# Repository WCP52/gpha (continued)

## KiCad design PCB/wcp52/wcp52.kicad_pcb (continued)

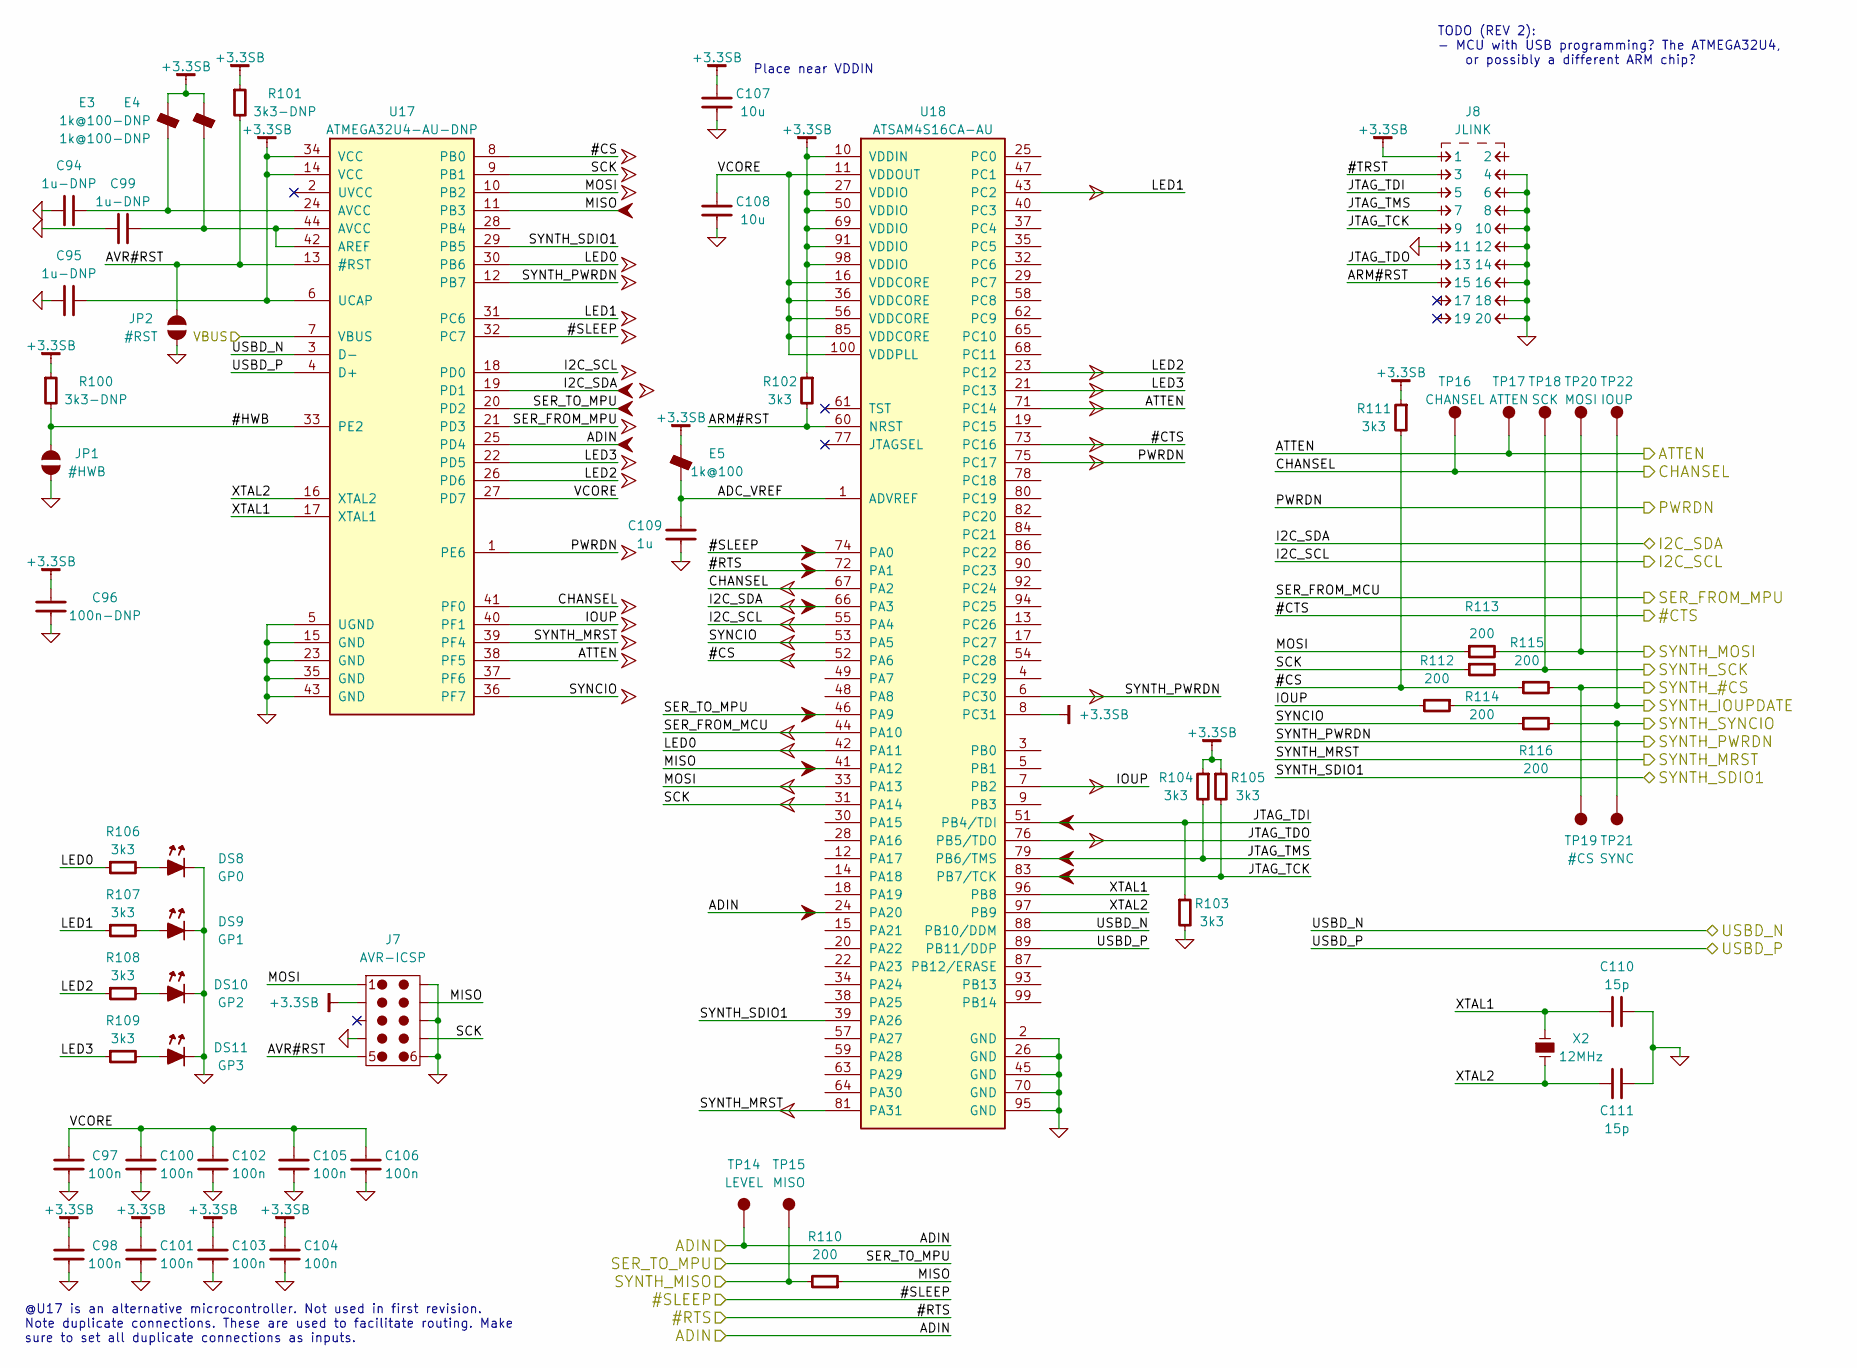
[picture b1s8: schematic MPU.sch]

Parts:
C94, C95, C99: 1u-DNP; CAPC2012X70
C96: 100n-DNP; CAPC1608X55
C97, C98, C100, C101, C102, C103, C104, C105, C106: 100n; CAPC1608X55
C107, C108: 10u; CAPC2012X70
C109: 1u; CAPC2012X70
C110, C111: 15p; CAPC1608X55
DS8: GP0; LED-0603
DS9: GP1; LED-0603
DS10: GP2; LED-0603
DS11: GP3; LED-0603
E3, E4: 1k@100-DNP; INDC1608X95
E5: 1k@100; INDC1608X95
J7: AVR-ICSP; TAGCONNECT-TC2050
J8: JLINK; CONN-100MIL-M-2x10-SHROUD
JP1: #HWB
JP2: #RST
R100, R101: 3k3-DNP; RESC1608X50
R102, R103, R104, R105, R106, R107, R108, R109, R111: 3k3; RESC1608X50
R110, R112, R113, R114, R115, R116: 200; RESC1608X50
TP14: LEVEL; TEST-SMD-SMALL
TP15: MISO; TEST-SMD-SMALL
TP16: CHANSEL; TEST-SMD-SMALL
TP17: ATTEN; TEST-SMD-SMALL
TP18: SCK; TEST-SMD-SMALL
TP19: #CS; TEST-SMD-SMALL
TP20: MOSI; TEST-SMD-SMALL
TP21: SYNC; TEST-SMD-SMALL
TP22: IOUP; TEST-SMD-SMALL
U17: ATMEGA32U4-AU-DNP; QFP80P1200X1200X120-44
U18: ATSAM4S16CA-AU; QFP50P1600X1600X160-100
X2: 12MHz; XTAL1200X480X460

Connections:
+3.3SB: C95.1, C96.1, C98.1, C101.1, C103.1, C104.1, C107.1, E3.1, E4.1, E5.1, J7.2, J8.1, R100.1, R101.1, R102.1, R104.1, R105.1, R111.1, U17.6 (UCAP), U17.14 (VCC), U17.34 (VCC), U18.8 (PC31), U18.10 (VDDIN), U18.27 (VDDIO), U18.50 (VDDIO), U18.69 (VDDIO), U18.91 (VDDIO), U18.98 (VDDIO); also elsewhere on the board
/Comm/#CTS: U18.73 (PC16); also elsewhere on the board
/Comm/#RTS: U18.72 (PA1); also elsewhere on the board
/Comm/#SLEEP: U17.32 (PC7), U18.74 (PA0); also elsewhere on the board
/Comm/IN_USBD_N: U17.3 (D-), U18.88 (PB10/DDM); also elsewhere on the board
/Comm/IN_USBD_P: U17.4 (D+), U18.89 (PB11/DDP); also elsewhere on the board
/Comm/SER_FROMUSB: U17.20 (PD2), U18.46 (PA9); also elsewhere on the board
/Comm/VBUS: U17.7 (VBUS); also elsewhere on the board
/MPU/#CS: R111.2, R115.1, U17.8 (PB0), U18.52 (PA6)
/MPU/#HWB: JP1.1, R100.2, U17.33 (PE2)
/MPU/#TRST: J8.3
/MPU/ADC_VREF: C109.1, E5.2, U18.1 (ADVREF)
/MPU/ADIN: TP14.1, U17.25 (PD4), U18.24 (PA20); also elsewhere on the board
/MPU/ARM#RST: J8.15, R102.2, U18.60 (NRST)
/MPU/ATTEN: TP17.1, U17.38 (PF5), U18.71 (PC14); also elsewhere on the board
/MPU/AVR#RST: J7.5, JP2.1, R101.2, U17.13 (#RST)
/MPU/CHANSEL: TP16.1, U17.41 (PF0), U18.67 (PA2); also elsewhere on the board
/MPU/I2C_SCL: U17.18 (PD0), U18.55 (PA4); also elsewhere on the board
/MPU/I2C_SDA: U17.19 (PD1), U18.66 (PA3); also elsewhere on the board
/MPU/IOUP: R112.2, U17.40 (PF1), U18.7 (PB2)
/MPU/JTAG_TCK: J8.9, R105.2, U18.83 (PB7/TCK)
/MPU/JTAG_TDI: J8.5, R103.1, U18.51 (PB4/TDI)
/MPU/JTAG_TDO: J8.13, U18.76 (PB5/TDO)
/MPU/JTAG_TMS: J8.7, R104.2, U18.79 (PB6/TMS)
/MPU/LED0: R106.1, U17.30 (PB6), U18.42 (PA11)
/MPU/LED1: R107.1, U17.31 (PC6), U18.43 (PC2)
/MPU/LED2: R108.1, U17.26 (PD6), U18.23 (PC12)
/MPU/LED3: R109.1, U17.22 (PD5), U18.21 (PC13)
/MPU/MISO: J7.9, R110.1, U17.11 (PB3), U18.41 (PA12)
/MPU/MOSI: J7.1, R113.1, U17.10 (PB2), U18.33 (PA13)
/MPU/PWRDN: U17.1 (PE6), U18.75 (PC17); also elsewhere on the board
/MPU/SCK: J7.7, R114.1, U17.9 (PB1), U18.31 (PA14)
/MPU/SER_FROM_MPU: U17.21 (PD3), U18.44 (PA10); also elsewhere on the board
/MPU/SYNCIO: R116.1, U17.36 (PF7), U18.53 (PA5)
/MPU/VCORE: C97.1, C100.1, C102.1, C105.1, C106.1, C108.1, U17.27 (PD7), U18.11 (VDDOUT), U18.16 (VDDCORE), U18.36 (VDDCORE), U18.56 (VDDCORE), U18.85 (VDDCORE), U18.100 (VDDPLL)
/MPU/XTAL1: C110.2, U17.17 (XTAL1), U18.96 (PB8), X2.1
/MPU/XTAL2: C111.2, U17.16 (XTAL2), U18.97 (PB9), X2.2
/Synth/#CS: R115.2, TP19.1; also elsewhere on the board
/Synth/IO_UPDATE: R112.1, TP22.1; also elsewhere on the board
/Synth/MASTER_RESET: U17.39 (PF4), U18.81 (PA31); also elsewhere on the board
/Synth/PWR_DWN_CTL: U17.12 (PB7), U18.6 (PC30); also elsewhere on the board
/Synth/SCLK: R114.2, TP18.1; also elsewhere on the board
/Synth/SDI: R113.2, TP20.1; also elsewhere on the board
/Synth/SDIO_1: U17.29 (PB5), U18.39 (PA26); also elsewhere on the board
/Synth/SDO: R110.2, TP15.1; also elsewhere on the board
/Synth/SYNC_IO: R116.2, TP21.1; also elsewhere on the board
GND: C94.2, C95.2, C96.2, C97.2, C98.2, C99.2, C100.2, C101.2, C102.2, C103.2, C104.2, C105.2, C106.2, C107.2, C108.2, C109.2, C110.1, C111.1, DS8.1, DS9.1, DS10.1, DS11.1, J7.4, J7.6, J7.8, J7.10, J8.4, J8.6, J8.8, J8.10, J8.11, J8.12, J8.14, J8.16, J8.18, J8.20, JP1.2, JP2.2, R103.2, U17.5 (UGND), U17.15 (GND), U17.23 (GND), U17.35 (GND), U17.43 (GND), U18.2 (GND), U18.26 (GND), U18.45 (GND), U18.70 (GND), U18.95 (GND); also elsewhere on the board
unnamed: C94.1, E3.2, U17.24 (AVCC)
unnamed: C99.1, E4.2, U17.42 (AREF), U17.44 (AVCC)
unnamed: DS8.2, R106.2
unnamed: DS9.2, R107.2
unnamed: DS10.2, R108.2
unnamed: DS11.2, R109.2

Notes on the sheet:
Place near VDDIN
@U17 is an alternative microcontroller. Not used in first revision. Note duplicate connections. These are used to facilitate routing. Make sure to set all duplicate connections as inputs.
TODO (REV 2): - MCU with USB programming? The ATMEGA32U4, or possibly a different ARM chip?

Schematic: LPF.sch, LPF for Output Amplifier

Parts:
C43, C44, C51, C52: 22p; CAPC1005X55
C45: 1p5; CAPC1005X55
C46, C49: 56p; CAPC1005X55
C47, C48, C50: 4p7; CAPC1005X55
L1: 56n; INDC1005X60
L2, L3: 47n; INDC1005X60

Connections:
/OutputAmp/LPF/A: C43.1, C44.1, C45.2, L1.2; also elsewhere on the board
/OutputAmp/LPF/B: C50.1, C51.1, C52.1, L3.1; also elsewhere on the board
GND: C43.2, C44.2, C46.2, C49.2, C51.2, C52.2; also elsewhere on the board
unnamed: C45.1, C46.1, C47.2, C48.2, L1.1, L2.2
unnamed: C47.1, C48.1, C49.1, C50.2, L2.1, L3.2

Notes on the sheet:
Intended frequency response of filter:

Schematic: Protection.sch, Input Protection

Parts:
DZ3, DZ4, DZ7, DZ8: ESD9L5.0ST5G; SOD-923
DZ5, DZ6: BZX84C2V7; SOT-23
R57, R58, R62, R63: 1k6; RESC1608X50
R59, R64: 3R3; RESC1608X50
R60, R61: 750; RESC1608X50

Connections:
+5: R60.2; also elsewhere on the board
-5: R61.1; also elsewhere on the board
/InputFrontend/IN1: R57.1, R58.1, R59.2; also elsewhere on the board
/InputFrontend/IN2: R62.1, R63.1, R64.2; also elsewhere on the board
/InputFrontend/Switching/IN1: DZ3.2, DZ4.1, R59.1; also elsewhere on the board
/InputFrontend/Switching/IN2: DZ7.2, DZ8.1, R64.1; also elsewhere on the board
GND: DZ5.1, DZ6.3, R57.2, R58.2, R62.2, R63.2; also elsewhere on the board
unnamed: DZ3.1, DZ5.3, DZ7.1, R60.1
unnamed: DZ4.2, DZ6.1, DZ8.2, R61.2

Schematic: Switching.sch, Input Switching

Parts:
C57, C58: 1n; CAPC1608X55
Q5: MMBT3906; SOT-23
Q6, Q7: 2N7002; SOT-23
R65: 1k6; RESC1608X50
R66: 10k; RESCAXE80P160X320X70-8
R67, R68: 200; RESC1608X50
U8, U9: MASWSS0162; SOIC127P600X175-8

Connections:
-5: Q6.2, Q7.2, R66.1; also elsewhere on the board
/InputFrontend/Buffer_Filter/IN: U8.8 (RF1), U9.8 (RF1); also elsewhere on the board
/InputFrontend/Switching/IN1: U8.5 (RF2); also elsewhere on the board
/InputFrontend/Switching/IN2: U9.5 (RF2); also elsewhere on the board
/MPU/CHANSEL: R65.1; also elsewhere on the board
GND: C57.2, C58.2, Q5.1, R66.6, R66.7, U8.1 (GND), U8.4 (GND), U8.6 (GND), U8.7 (GND), U9.1 (GND), U9.4 (GND), U9.6 (GND), U9.7 (GND); also elsewhere on the board
unnamed: C57.1, R67.2, U8.2 (BIAS_A), U9.3 (BIAS_B)
unnamed: C58.1, R68.2, U8.3 (BIAS_B), U9.2 (BIAS_A)
unnamed: Q5.2, R65.2
unnamed: Q5.3, Q6.1, R66.8
unnamed: Q6.3, Q7.1, R66.3, R67.1
unnamed: Q7.3, R66.2, R68.1

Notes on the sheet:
Inside shield
Outside shield
GaAs switch bias and truth table:
-5V
3V3
0V7
Low = -5V High = 0V
BIAS_A
BIAS_B
SWITCH
Closed
Open, terminated
Open, unterminated
Closed, terminated
CTRL
@U8:BIAS_A @U9:BIAS_B
@U8:BIAS_B @U9:BIAS_A
SELECTED
IN2
IN1

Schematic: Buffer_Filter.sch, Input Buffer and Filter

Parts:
C59: 100n; CAPC1608X55
C60, C62: 22p; CAPC1608X55
C61: 33p; CAPC1608X55
L4, L5: 39n; INDC1005X60
Q8: MMBT3904; SOT-23
Q9, Q10: BFR540; SOT-23
R69, R70, R71, R72: 200; RESC1608X50
R73: 1k6; RESC1608X50
R74: 30; RESC1608X50
R75, R76, R77: 100; RESC1608X50

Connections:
+5: Q9.3; also elsewhere on the board
-5: C59.2, Q8.2, R74.2; also elsewhere on the board
/InputFrontend/Buffer_Filter/IN: Q9.1, R69.1, R70.1, R71.1, R72.1; also elsewhere on the board
/InputFrontend/Detector/IN: C62.1, L5.1; also elsewhere on the board
/Synth/OUT1: R75.1, R76.2; also elsewhere on the board
GND: C60.2, C61.2, C62.2, R69.2, R70.2, R71.2, R72.2, R73.1, R75.2; also elsewhere on the board
unnamed: C59.1, Q8.3, Q10.1, R73.2
unnamed: C60.1, L4.2, R76.1, R77.1
unnamed: C61.1, L4.1, L5.2
unnamed: Q8.1, Q10.2, R74.1
unnamed: Q9.2, Q10.3, R77.2

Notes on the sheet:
Inside shield
Outside shield

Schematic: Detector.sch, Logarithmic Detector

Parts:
C63, C65, C67: 10n; CAPC1608X55
C64, C66: 1u; CAPC2012X70
C68: 100n; CAPC1608X55
C69: 47u; CAPC3216X70
C70: 220p; CAPC1608X55
C71: 330n; CAPC1608X55
R78: 3k3; RESC1608X50
R79: 53R6; RESC1608X50
R80: 49R9; RESC1608X50
U10: AD8310ARMZ; SOP65P490X109-8

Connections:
+5: R80.1; also elsewhere on the board
/InputFrontend/Detector/4V6_FILTERED: C67.1, C68.1, C69.1, R80.2, U10.5 (VPOS), U10.7 (ENBL)
/InputFrontend/Detector/IN: C63.2, C64.2, R78.1, R79.1; also elsewhere on the board
/InputFrontend/Detector/OUT: U10.4 (VOUT); also elsewhere on the board
GND: C65.2, C66.2, C67.2, C68.2, C69.2, C70.1, C71.2, R78.2, R79.2, U10.2 (COMM); also elsewhere on the board
unnamed: C63.1, C64.1, U10.8 (IN+)
unnamed: C65.1, C66.1, U10.1 (IN-)
unnamed: C70.2, U10.6 (BFIN)
unnamed: C71.1, U10.3 (OFLT)

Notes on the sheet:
Inside shield

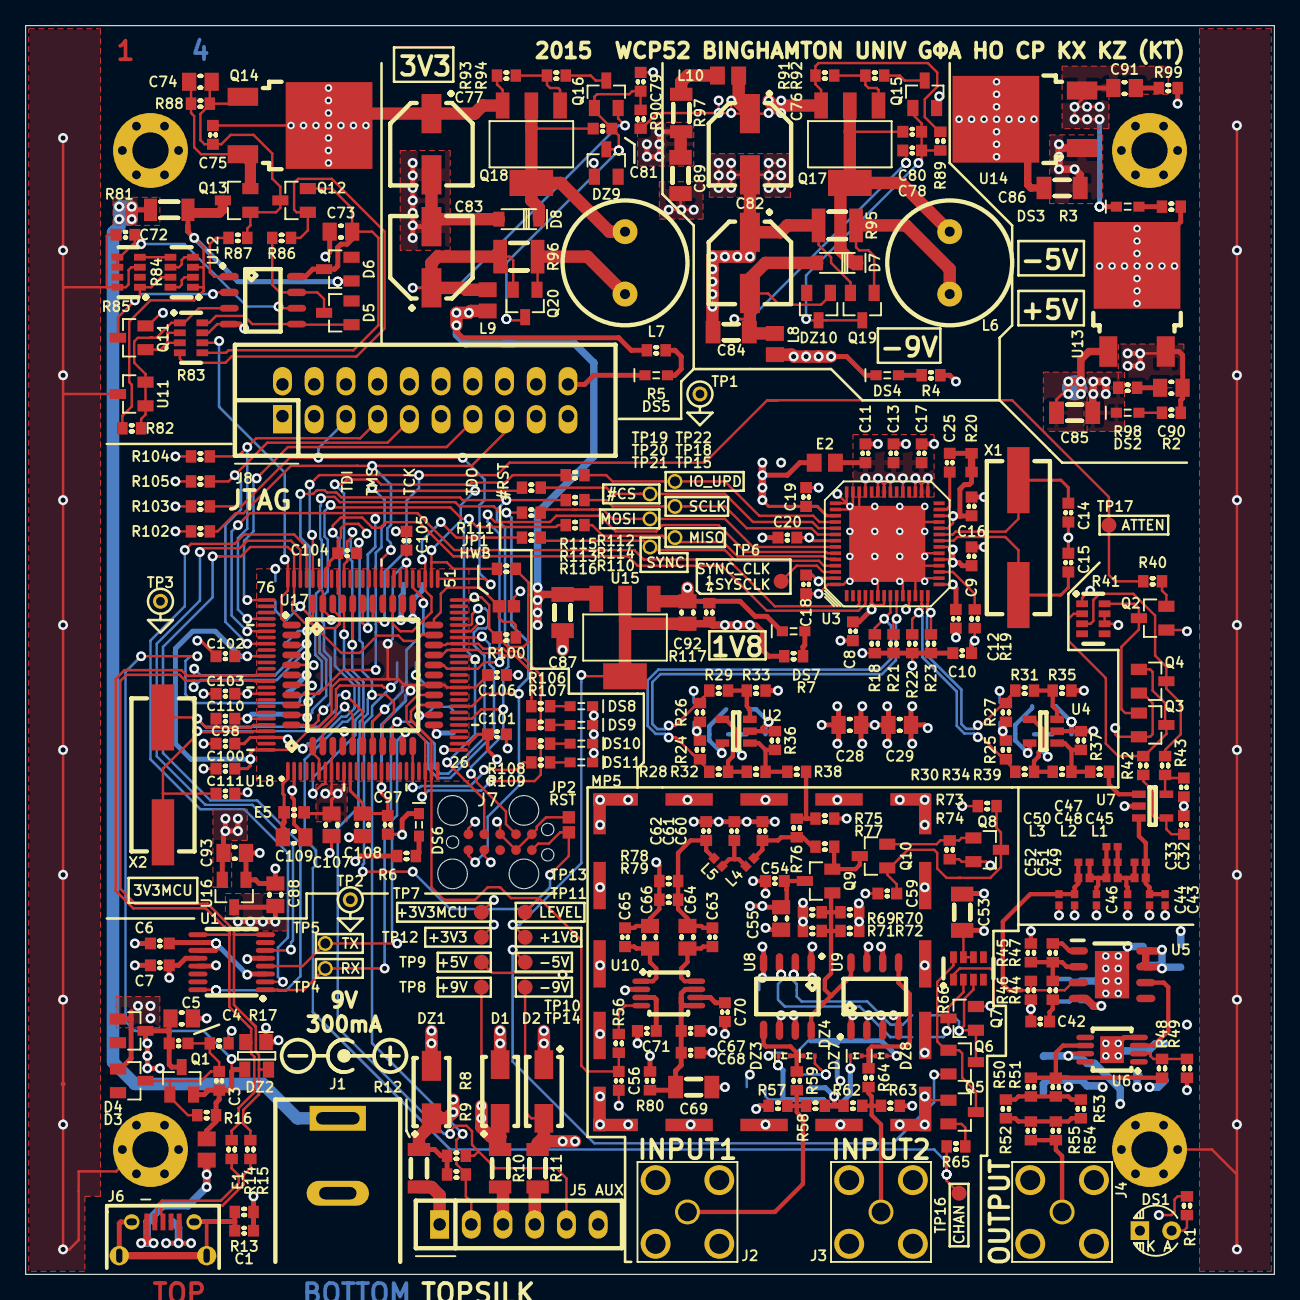
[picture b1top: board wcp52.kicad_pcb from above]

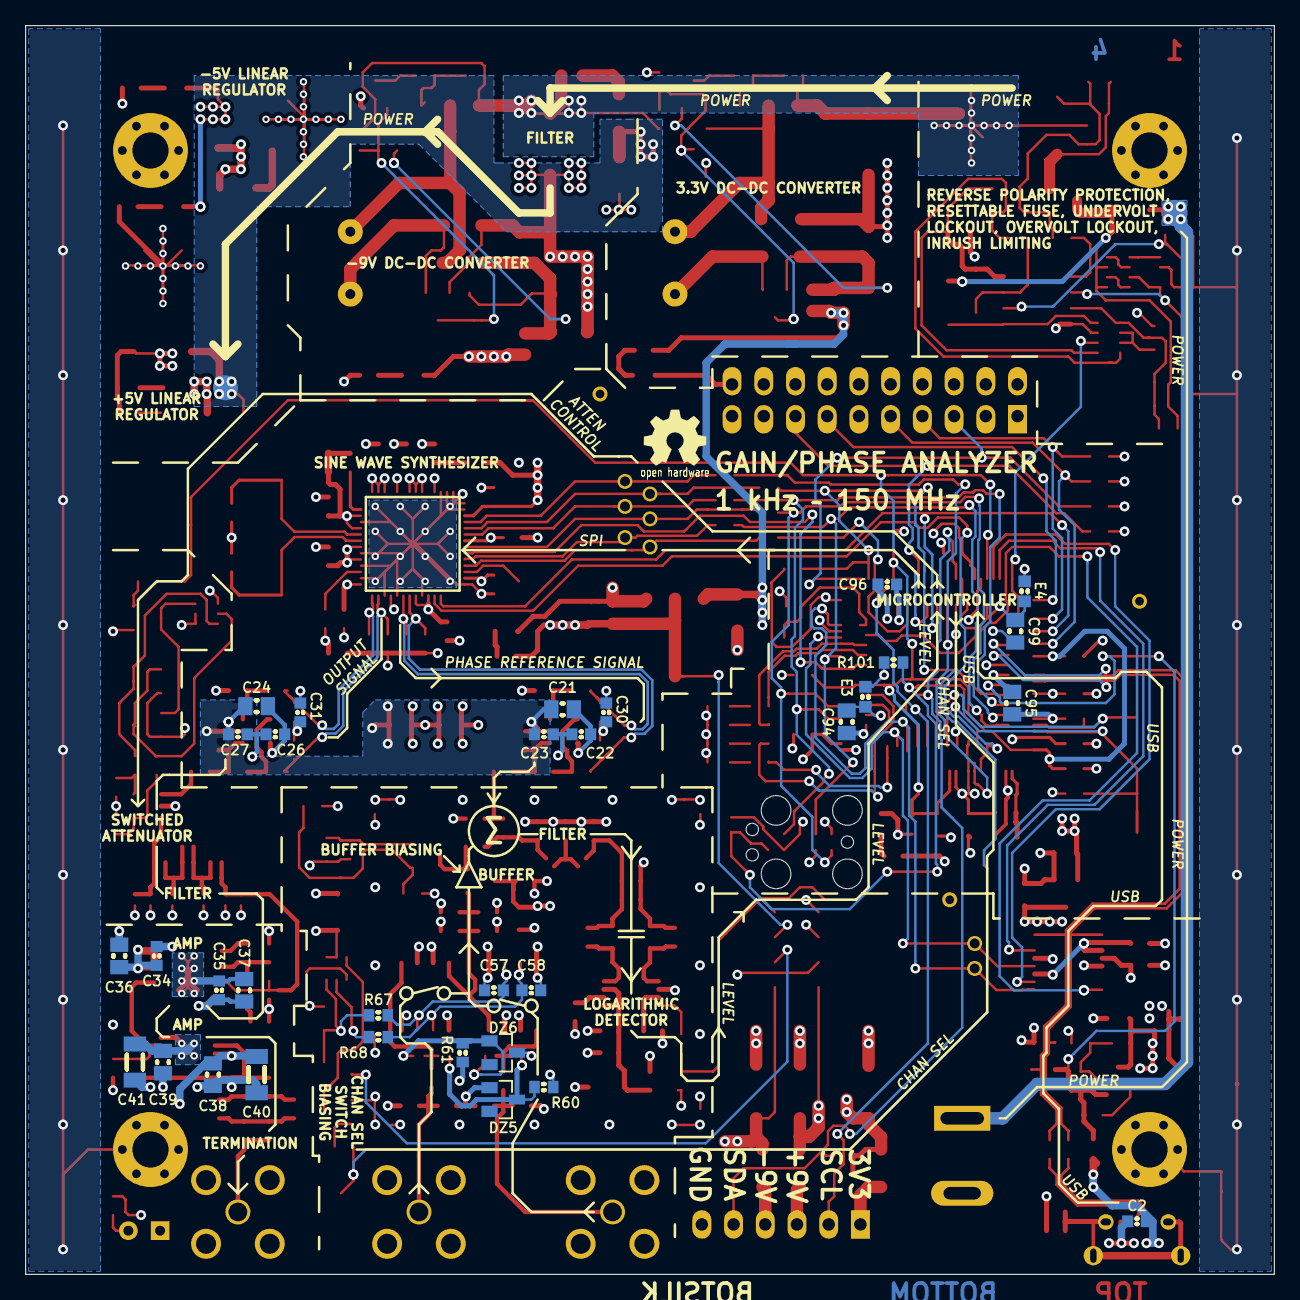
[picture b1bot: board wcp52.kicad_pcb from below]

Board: 4 copper layers, 100.0 x 100.0 mm, 349 parts (32 on the bottom side), 170 nets.

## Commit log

2015-03-15 Began writing manual
2015-03-15 writewritewrite
2015-03-15 Marked power splitter as optional
2015-03-15 Added diagrams
2015-03-16 Added more descriptions
2015-03-16 Added title page
2015-03-16 Allow "make clean" to remove a bit more cruft
2015-03-16 Split into files
2015-03-16 Indentation changes
2015-03-16 Added block diagram description
2015-03-18 Add BOM/schematic
2015-03-18 More BOM work
2015-03-18 Schematic fixed
2015-03-21 Added GaAs section
2015-03-21 Formatting
2015-03-21 Synthesizer section
2015-03-21 Updated BOM
2015-04-01 Propagated updates from schematic
2015-04-01 Changed style of numbers/units
2015-04-01 Corrected for post-testing revisions
2015-04-01 Added description of buffer
2015-04-01 Added graphics for synthesizer section
2015-04-01 Added more text
2015-04-02 Work on manual
2015-04-11 Move files into OwnersManual
2015-04-11 Add initial files
    LED blink works, USART does not.
2015-04-11 Fix screwed-up repo
2015-04-11 Add work in SPI_try
    Not really sure... we're going to delete this code anyway.
2015-04-11 Add final firmware. Again.
2015-04-11 Add non-functional synth code
2015-04-11 Add Makefile-built code
2015-04-11 Fix build system - wasn't linking everything
2015-04-11 Fix Atmel's code - emits warnings!
    Shame on you Atmel.
2015-04-11 Start refactoring code to synth.c, synth.h
2015-04-11 Refactor synth code more
2015-04-11 Clean up excess in main
2015-04-11 Add work on programming, serial
2015-04-11 Add debugging
2015-04-11 Fix serial code
2015-04-11 Do not compile with optimization
2015-04-11 Remove hard-coded frequency
2015-04-11 Use floating-point printf
2015-04-11 Remove old Atmel Studio stuff
2015-04-11 Rename new stuff
2015-04-11 Remove SPI_try
2015-04-11 Change tabs to spaces
2015-04-11 Clone in scpi-parser
2015-04-11 Automatically compile all C sources
2015-04-11 Add working SCPI parser
    All commands are example commands from the SCPI library
2015-04-11 Implement TEST:LEDON, TEST:LEDOFF
2015-04-11 Write SCPI reset function
2015-04-11 Completely remove old command parser
2015-04-11 Set *IDN? string
2015-04-11 Move sources into src/
2015-04-11 Move Test:* commands to separate file
2015-04-11 Fix comment
2015-04-11 Fix some SCPI parameters
2015-04-11 Use new SCPI_CmdId to clean up code
2015-04-11 Communication tweaks
2015-04-11 Use SCPI_IsCmd
2015-04-11 Move config/ into src/
2015-04-11 Combine multiple set/clear commands
2015-04-11 Use int_fast8_t in util_set_pin
2015-04-11 Add SYNCIO pin to Test:SET
2015-04-11 Fix clock polarity
2015-04-11 Fix coding style
2015-04-11 Add amplitude and phase control code
    added monkeybutts of SPI ampltude and phase
2015-04-11 Add comments
2015-04-11 Use register length names instead of magics
2015-04-11 Fix amplitude control
    Setting wrong bit for Amplitude Multiplier Enable
2015-04-11 Add Test:SAMple (no ADC code yet)
2015-04-11 Lots of changes checked in late...
2015-04-11 Fix phase bug - channels were not phase-locked
2015-04-11 Temporary commit
2015-04-11 Revert "Temporary commit"
    This reverts commit 2f33baf6dfdd27b3e39f1499db614684b5c031f0.
2015-04-11 Replace Atmel Makefile with own version
2015-04-11 Makefile tweaks
2015-04-11 Add USB driver
2015-04-11 Clean up Makefile
2015-04-11 Set VID/PID (might be temporary)
2015-04-11 Clean up old files
2015-04-11 Add dep-files to 'make clean', remove gdb scripts
2015-04-11 Migrate code to new PCB
2015-04-11 Change MCU to ATSAM4S4C
2015-04-11 Add new programmer config
2015-04-11 Compiles and runs on final PCB
2015-04-11 Fix silly USB bug
    Second PLL was not enabled
2015-04-11 Work on integrating stdio with USB
2015-04-11 Add working USB communications
2015-04-11 Change VID/PID, clean up conf_usb.h
2015-04-11 Code cleanup
2015-04-11 Update scpi-parser from upstream
2015-04-11 Use pio.h instead of gpio.h
    Removes unnecessary level of abstraction
2015-04-11 Add lowlevel pin control
    LOWlevel:SETpin
    LOWlevel:CLRpin
    LOWlevel:GETpin
    LOWlevel:LISTpins
2015-04-11 Move xmacros out of main functions
2015-04-11 Remove scpi-parser submodule
2015-04-11 Move files into Firmware
2015-04-11 Add block diagram
2015-04-11 Add scripts
2015-04-11 Add synth schematic
2015-04-11 Add output amplifier schematic
2015-04-11 Add frontend
2015-04-11 Add power input circuit
2015-04-11 Add DC-DC
2015-04-11 Complete power supply design
2015-04-11 Finish USB subcircuit
2015-04-11 Begin adding MCU
2015-04-11 Start PCB
2015-04-11 Begin swapping MCU
2015-04-11 PCB work, mostly mechanical
2015-04-11 Layout most analog bits
2015-04-11 Add side bars, ground plane
2015-04-11 Lots of routing
2015-04-11 Lots of layout work
2015-04-11 Some PCB work
2015-04-11 All parts placed
2015-04-11 Some power layout
2015-04-11 Power plane layout
2015-04-11 Major layout work - almost done
2015-04-11 Place final traces
2015-04-11 Add I2C to header
2015-04-11 Clean up silkscreen
2015-04-11 Add overload protection to aux power output
2015-04-11 Add some test points
2015-04-11 Tidy up F.Cu
2015-04-11 Tidy up In1.Cu
2015-04-11 Add more 3D models
2015-04-11 Connect attenuator control
2015-04-11 Add power LED
2015-04-11 Some work removing unnecessary bits
2015-04-11 Clean up resistor BOM
2015-04-11 Tweak layout
2015-04-11 Swap 0402 to 0603, add USB inrush protection
2015-04-11 Touch up PCB
2015-04-11 Add test LEDs
2015-04-11 Set unnecessary FT230 parts "DNP"
2015-04-11 Add postprocessing
2015-04-11 Swap inner layers
2015-04-11 Add legends to Gerbers
2015-04-11 Add SPI series resistors
2015-04-11 Fix page sizes
2015-04-11 Fix paste mask
2015-04-11 Update 3D render
2015-04-11 Touchups
2015-04-11 Quick adjustment of silkscreen designator
2015-04-11 Add alternative MCU
2015-04-11 Connect ICSP for new MCU
2015-04-11 Tweaks
2015-04-11 Reorganize files
2015-04-11 Render converter only runs when necessary
2015-04-11 Minor routing fixes
2015-04-11 Route DDS's SDIO1 to MCUs
    Just in case...
2015-04-11 Add #CS pullup resistor
2015-04-11 Route UART to alt MCU
2015-04-11 Set min. mask width properly
2015-04-11 Reorganize MPU schematic
2015-04-11 Add reset jumper
2015-04-11 Connect #SLEEP to AVR
2015-04-11 Quick gitignore/Makefile tweaks
2015-04-11 Remove unlocked-unit parts
2015-04-11 Fix NPTH issue
2015-04-11 Minor silk/routing/thermal pad fixes
2015-04-11 Paste mask fixes
2015-04-11 Route LEDs to AVR
2015-04-11 Remove extra connections
2015-04-11 Add PSU filter inductors
2015-04-11 Test point fixes
2015-04-11 Add back drawing
2015-04-11 Add panel power LED
2015-04-11 Add power rail diag LEDs
2015-04-11 Move ATTEN test point to near attenuator
2015-04-11 Quick tweaks, renders
2015-04-11 Reannotate parts. May need to tweak silkscreen
2015-04-11 Silkscreen tweaks, renders
2015-04-11 Correct spacing of USB differential pair
2015-04-11 Schematic touchups
2015-04-11 Minor silkscreen fix
2015-04-11 Change schematic pages to letter size
2015-04-11 Correct BOM lines
    The BOM reader currently cannot interpret things like '3k3'.
2015-04-11 BOM fixes
2015-04-11 Prepare to fab
2015-04-11 BOM line fixes
2015-04-11 BOM corrections/combinations, etc
    Add configuration for bomtool
    Remove old schematic file no longer used
2015-04-11 Widen tolerance on a capacitor
2015-04-11 More BOM stuff
2015-04-11 BOM stuff
2015-04-11 Schematic/doc work
2015-04-11 Schematic updates for documentation
2015-04-11 More doc fixes
2015-04-11 Nicer BOM lines
2015-04-11 Add post-testing revision, todo notes
2015-04-11 Fix BOM
    D5 was removed, so should not be in the BOM
2015-04-11 Move files into PCB/
2015-04-11 Add and adjust simple readme/license files
2015-04-11 Remove GCC extensions
2015-04-15 Remove cruft from .gitignore
2015-04-16 Program with J-Link
2015-04-16 Began a getting started section in the owner's manual
2015-04-16 Finished text for getting started. Needs a review and some pics
2015-04-16 Fixed a figure
2015-04-16 Adjust formatting and syntax in Getting Started
2015-04-19 Update documentation
    Correct LaTeX Makefile: don't include README.rst
    Add local .gitignore
    Add microcontroller documentation
    Update schematic renders
2015-04-19 Add Thumbs.db to gitignore
2015-04-20 added to software.tex still need to add stuff though
2015-04-23 Tidy up gitignores
2015-04-28 added to software section of manual still need to fix formatting though its definitely not right
2015-05-06 added SCPI code to the users manual
2015-05-06 Clean up after Harrison
    Dammit Harrison
2015-05-07 Update to getting started guide
2015-05-07 Render manual
2015-05-07 Add status LED
2015-05-08 Fixed spelling errors in getting started
2015-05-17 Add initial CLI
2015-05-17 Correct two docstrings
